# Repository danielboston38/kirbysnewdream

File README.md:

# Link to Video

A replacement for the RF modulator in the original Nintendo Entertainment System (NES-001). Drops into the stock RF module slot inside the shell and provides composite video and USB-C power in place of a part that fails by design.

> **Renamed.** This project shipped its first revision as **Kirby's New Dream**.
> From v2 onward it is **Link to Video**. Anything referring to the old name —
> the v1 board silkscreen, the 2026-07-16 PCBWay fab package under
> [`pcbway_production/`](./pcbway_production), and older commits — is the same
> project. The GitHub repository was renamed to match; the previous
> `kirbysnewdream` URL still redirects.

## Why this board exists

The NES-001's RF modulator already carries composite video, so this isn't about
adding an output the console lacks. It's about replacing a part that reliably
destroys itself.

Nintendo packed the modulator's regulator and RF stages into a sealed can with no
ventilation. It cooks its own electrolytics, they leak, and the electrolyte eats
the traces underneath. Across three NES-001 units on the author's bench, **all
three** had modulator failures from exactly this — including a Mitsumi unit that
looked pristine externally and had every capacitor leaking inside.

So the modulator is a consumable on a forty-year-old console, and the usual
options are to recap a corroded board or to fit an aftermarket board. This is the
second option, with the power input modernised to USB-C while the slot is open.

## Disclosure

This project's schematic design, debugging, and documentation were developed with the assistance of AI (Claude, by Anthropic). All hardware was hand-assembled, tested, and validated by the author. Use, review, and verify independently before building.

## Status

🟡 First prototype assembled and power-tested successfully (5V confirmed clean on rail, no protection trips). Video output path **does not work on v1 hardware** — traced to a schematic defect in which Q1's emitter node was shorted to the +5V rail (see Known Issues). Fixed in source; v1 boards need a rework.

<!-- Swap the line above for something like this once video's confirmed:
🟢 Fully validated — power and composite video both confirmed working on hardware.
-->

## Features

- USB-C power input (power only — no data lines)
- Composite video output
- Active overcurrent protection — TPS2553 eFuse with a ~1.18 A resistor-programmed limit, soft-start and thermal shutdown, backed by a polyfuse
- Fits inside the original NES shell at the stock RF module location
- Bring-up test points for video, ground, +5V and audio, labelled on the silkscreen
- Feed header for an external 8-pin mini-DIN RGB connector (NESRGB)
- All resistor and capacitor values printed on the silkscreen — the v1 board had four identical unlabelled axial footprints carrying four different values, which caused three separate wrong-resistor build errors
- 2-layer PCB, designed in KiCad

## Power path

```
USB-C  ──  F1 polyfuse  ──  U1 TPS2553 eFuse  ──  +5V rail  ──  J4.3 → NES
  VBUS      2.0A hold        ~1.18A limit          C1 100µF
            3.8A trip        soft-start            D1 TVS
            (backup)         thermal shutdown
```

F1 alone trips at 3.8 A, which protects nothing on a console that draws
roughly 0.5–0.7 A. U1 is the real protection; F1 stays as a backup in case
the eFuse ever fails short.

The current limit is set by R6 on U1's ILIM pin. The relationship is
**inverse** — a larger resistor gives a *lower* limit:

| R6 | Limit (typ) |
|---|---|
| 15 kΩ | 1700 mA |
| 20 kΩ | 1295 mA |
| **22 kΩ (fitted)** | **~1180 mA** |
| 49.9 kΩ | 520 mA |
| 210 kΩ | 130 mA |

Roughly I_OS(A) ≈ 25.9 / R6(kΩ), valid over TI's recommended 15 kΩ–232 kΩ.

U1's EN (pin 3) is active-high and tied to its own input, so the switch is
always on. FAULT (pin 4) is an open-drain output left unconnected — there is
nothing inside a closed NES shell to indicate to. If you want fault
indication, it can sink 25 mA directly.

A useful side effect: D1 is a unidirectional TVS, so fitting it backwards
puts a forward-biased diode across the 5 V rail. Before U1 that was a near
short relying on a polyfuse taking seconds to react. Now the eFuse current-
limits it at ~1.18 A and thermally shuts down, so the mistake is
self-limiting rather than destructive.

## Test points (v2)

Four through-hole test points (2.0 mm pad, 1.0 mm drill) for bring-up. They accept
a 0.64 mm square header pin, so you can solder pins in and use scope grabbers.

The silkscreen carries the signal name only — `VIDEO`, `GND`, `+5V`, `AUDIO` — so
the board reads without this table. The refdes lives on F.Fab for the fab drawings.
(On v2's first pass this was backwards: the signal names were on F.Fab, which never
reaches the physical board, so the silkscreen said only `TP1`–`TP4`.)

| TP  | Net          | Location (mm) | Notes |
|-----|--------------|---------------|-------|
| TP1 | `/VIDEO_OUT` | 62.0, 60.0    | Jack-side video, i.e. after C2 and the 75 Ω series R5 — what the TV actually sees. A high-impedance probe reads roughly double the terminated amplitude. |
| TP2 | `GND`        | 58.5, 60.0    | Straight into the B.Cu ground pour. |
| TP3 | `/5V`        | 52.0, 43.1    | Sits directly on the protected 5 V trunk, downstream of F1 and the TPS2553. |
| TP4 | `/AUDIO_OUT` | 65.9, 28.35   | Audio pass-through between J4 pin 2 and J2. |

The whole back layer is a ground pour, so TP2's position is a convenience, not a
constraint — you can clip a ground lead to any B.Cu feature.

To probe the buffer itself rather than its output, use Q1's emitter leg directly;
there is no test point on `Net-(Q1-E)`.

## RGB output (v2)

Provision for the [NESRGB](https://etim.net.au/nesrgb/) board's RGB connector —
the Micomsoft XRGB-mini Framemeister 8-pin mini-DIN standard.

The connector itself is **not** on this board. The NESRGB kit ships it as a
panel-mount jack that epoxies into a 12 mm hole in the shell, so this board just
feeds it. R/G/B run directly from the NESRGB to the connector; we supply the
other three pins on **J5**:

| J5 pin | Net          | mini-DIN pin | |
|--------|--------------|--------------|---|
| 1 | `/RGB_VIDEO` | 3 | Composite video / sync, 75 Ω terminated |
| 2 | `GND`        | 4 | |
| 3 | `/5V`        | 5 | Downstream of the TPS2553, so it is current-limited |

mini-DIN pins 1 and 2 are N/C; pins 6, 7 and 8 are Blue, Green and Red from the
NESRGB. Note the standard carries no audio — that stays on the RCA jack, which is
deliberate on Tim Worthington's part (it keeps video noise out of the audio).

**Why R7 exists.** The video buffer's output (`/VIDEO_BUF`, Q1's emitter through
C2) now feeds two outputs. Each needs its own 75 Ω source termination: R5 for the
RCA jack, R7 for the mini-DIN. Tying both to one resistor would put two 75 Ω loads
in parallel and halve the amplitude whenever both cables are plugged in.

**One output at a time.** Composite and RGB are an either/or — the design does not
target using both at once. Whichever cable is plugged sees a correct 75 Ω source,
and the unused branch is an unloaded stub.

If both are ever plugged in simultaneously, R7 means each still gets a properly
terminated 75 Ω source rather than the halved amplitude you'd get from sharing one
resistor. Q1's drive is the limit in that case, and it is why **R1 is 220 Ω from
v2** rather than the original 330 Ω. Simulated in ngspice with 2 Vpp at the tap
and both outputs terminated: at 330 Ω the follower clips the positive (white)
peaks by 33 %, at 220 Ω by 11 %. With a single output loaded — the supported
mode — 220 Ω is clean and symmetric (+0.439 / −0.447 V at the jack). Simulated,
not measured on hardware, and still not a supported mode.

## Hardware

- Designed in KiCad (schematic + PCB source included in this repo)
- Fabricated via PCBWay
- See [BOM.csv](./BOM.csv) for full parts list

## Build Notes / Known Issues (v1)

- **Q1 emitter node shorted to +5V (breaks video).** Q1's emitter is clamped to the rail, so C2 couples +5V — not video — into R5/J3. The exact wiring differs by revision: in the repo's pre-v1.1 source R1 had *both* ends on `/5V`, while the fabbed 2026-07-16 boards have R1 pad 1 on `/5V` and pad 2 on a separate net with C1 only. Root cause: an R2 (110Ω) was deleted from the schematic on 2026-07-04, and KiCad merged the two leftover collinear wire stubs into one wire, welding the emitter node to `/5V`. Fixed in source as of v1.1. **Rework for an existing board** (applies to the boards fabbed from the 2026-07-16 gerbers, whose IPC netlist reads `/5V = J4.3, F1.1, R1.1, Q1.1, C2.1, D1.1` and `Net-(C1-Pad1) = R1.2, C1.1`):

That revision has two defects — Q1's emitter is clamped to the rail, *and* C1 only reaches the rail through R1, so the bulk cap decouples nothing. Both are fixed together:

**Confirm the diagnosis before you cut.** Power off, unplugged, caps discharged.
Probe +5 V at J4 pin 3 or D1's K-marked lead. Two measurements, mirror images of
each other:

| Measurement | Defective board | Correctly wired |
|---|---|---|
| Q1 emitter → +5 V | **~0 Ω** | ~330 Ω (R1) |
| C1 **+** terminal → +5 V | **~330 Ω** (stranded behind R1) | ~0 Ω |

After the rework these swap. To identify Q1's legs without relying on the TO-92
orientation: the leg reading 0 Ω to GND is the collector, the leg with continuity
to J4 pin 1 is the base, and the remaining one is the emitter.

Two tests that look useful but are not:

- **Emitter → J3 tip.** C2 blocks DC, so this reads open either way.
- **C1 + → Q1 emitter.** Reads ~330 Ω on a good board *and* a bad one, because R1
  sits between them in both wirings. It cannot distinguish the two.

Powered, the fastest single check is DC at Q1's emitter: roughly 1.5–3 V if
correct, sitting at exactly the rail voltage if shorted.

**R1's left pad is a star point.** Three things meet there: F1 (the source), the
D1 + J4.3 branch (the load), and Q1's emitter. The two incoming rail traces are
*collinear*, so a single cut severs both — which is why this needs **two**
jumpers, not one.

1. **Cut** the 0.8 mm trace leaving R1's left pad toward the **upper left**, about
   5–8 mm from the pad. Leave the trace entering from the upper right — that is
   Q1's emitter and must stay. Stay below the level of D1's cathode; above that
   point only one of the two overlapping traces is present, and you need both cut.

2. **Two jumpers.** The cut leaves three islands that must all become one rail:

   | Island | Pads |
   |---|---|
   | A | C1's **+** pad, R1's **right** pad |
   | B | F1 pad 1 (left pad, trace toward D1 — not the USB-C side) |
   | C | D1's cathode (K), J4 pin 3 |

   Any two wires joining all three work. One wire per pad:
   - **C1+ → F1 pad 1** (~14 mm)
   - **R1's right pad → D1 cathode** (~25 mm)

   Do this with R1 removed — its right pad is far easier to solder empty.

3. **Fit R1 = 300–330 Ω.** Check the part before fitting: R1, R3, R4, R5 (and R7
   on v2) all share the same `R_Axial_DIN0207` footprint in four different values,
   and the v1 silkscreen prints no values. At least one board was built with a
   5.1 kΩ from the R3/R4 pile in R1, which gives ~0.6 mA of standing current
   instead of ~9 mA — enough to look plausible and still produce no usable video.

4. **Confirm R5 (75Ω) is populated.** Across R5's own pads should read ~75 Ω; it
   has no parallel path in circuit (C2 blocks DC on one side, the jack is open on
   the other), so it doubles as a meter sanity check.

5. **Fit the transistor last.** Powering the board before the cut is done drives
   Q1 into saturation from the rail straight to ground with no current limit — see
   below.

Verify with a meter before powering: R1's left pad to D1 cathode must now read
**open**; R1's left pad to F1 pad 1 must read **~330Ω** through R1; R1's left pad
must still show continuity to Q1's emitter and C2 pin 1; and D1's cathode must
read **~0 Ω** to J4 pin 3 *and* to F1 pad 1. Powered, Q1's emitter should sit near
1.5–3V — a reading of 5V means the cut did not take.

**The short destroys transistors.** With the emitter clamped to +5 V and the base
at the NES's video level, the B-E junction is forward-biased by 3–4 V, so Q1
saturates with its collector tied directly to ground and nothing limiting the
current. Q1 is a 150 mA part; F1 does not trip until 3.8 A. Every power-up in that
state risks another transistor, which is the likely fate of the first one.
- F1 (polyfuse) footprint field in KiCad is mislabeled as a polarized capacitor footprint despite correct value — cosmetic/documentation issue only, does not affect function. Fix planned for v2.
- Video/audio RCA jack mounting holes are slightly asymmetric — cosmetic only, doesn't affect NES shell fit.
- v1 silkscreen doesn't include component value labels or Q1 pin markers (E/C/B). **Values are on the silkscreen from v2.** On v1 this caused three separate wrong-resistor errors in R1 (a 5.1kΩ and an 820Ω both fitted before the right value went in) because R1/R3/R4/R5/R7 share one footprint across four values. Q1 pin markers are still outstanding.
- **D1 does not protect U1.** The fitted TVS is a Littelfuse 1.5KE6.8A: stand-off 5.80 V, breakdown 6.45–7.14 V at 10 mA, clamping 10.5 V at 144.8 A. The TPS2553's absolute maximum on IN and OUT is 7 V, so the TVS has barely begun conducting by the time the eFuse is already out of spec, and under a real surge it lets the rail reach 10.5 V. D1 protects the console downstream; it will not save U1. Repositioning D1 doesn't help — both U1 pins share the same 7 V rating — and no avalanche TVS clamps below 7 V while standing off USB-C's 5.5 V worst case. Proper protection needs a switch with integrated overvoltage cutoff. Deferred to v3 — v2 ships with this gap.
- D1's symbol (`Diode:1.5KExxA`) names both pins A1/A2 and draws no cathode — KiCad uses identical pin naming for the unidirectional and bidirectional variants of this part. Polarity comes only from the footprint silkscreen band, which is at the pad-1 (+5 V) end and is correct. Watch this when hand-assembling.

## Video input biasing

Q1's base is DC-coupled straight to the NES video line, with no bias network on
this board. That is deliberate, and it took a long bench session to establish
why it works.

**The NES mainboard supplies a 1 kΩ pulldown on its video output pin.** Measured
in circuit at 0.999 kΩ, identical with the meter leads both ways — a real
resistor, not a semiconductor junction. Q1's base sources roughly 46 µA, which
that 1 kΩ absorbs in about 46 mV. The base cannot float up and Q1 cannot cut off.

This is the same reason Nintendo's own modulator has no base pulldown either. It
also matches the load Nintendo presented on that pin: a 330 Ω series resistor
into a 5.6 kΩ / 330 Ω divider, roughly 500 Ω in total. The NES is built to drive
a few hundred ohms.

**So no base pulldown, and no input coupling cap.** If you are adapting this
design to something other than an NES-001, measure that pin to ground first —
if it reads open, you need a pulldown (~47 kΩ) and this board does not have one.

**R2 (330 Ω) is not a bias resistor.** It sits in series between J4 pin 1 and
Q1's base, mirroring the 330 Ω Nintendo places in the same position. Against
Q1's ~21 kΩ base input impedance it costs nothing in signal terms; what it buys
is fault-current limiting into the base-emitter junction, whose reverse rating
is only 5 V.

## Design checks

Two safety nets sit alongside ERC and DRC, both aimed at faults this board has
actually shipped with.

### `tools/check_nets.py`

```
python3 tools/check_nets.py
```

Exports the schematic netlist, reads the PCB's pad nets, confirms the two agree,
and asserts a set of invariants — chief among them that **Q1's emitter is not on
any power net**. That was the v1 fault: the emitter follower's output was tied
to +5V along with J4.3, D1.1 and F1.1, so Q1 saturated into a grounded collector
with nothing limiting the current. It destroyed a transistor on every power-up.

**ERC and DRC both passed cleanly on that board.** Neither can see that a net is
*wrong*, only that it is internally consistent — which is exactly why this check
exists. Run it before generating a fab package. Gerbers carry no net information,
so once you have them the mistake is invisible.

### `nes_power_video.kicad_dru`

Custom DRC rules covering the geometric half: extra clearance between Q1's
emitter and base nodes and the supply rails, and between the two USB-C
configuration channels. These catch the layout-adjacency version of the same
mistakes. They cannot catch a wrong net assignment — DRC has no view of design
intent — which is what the script above is for.

## Assembly

<!-- Add step-by-step or reference photos here once you've got a documented build process -->

Refer to BOM.csv for exact part values and footprints. Every component carries
its sourcing data in two places, kept in step: the `Manufacturer`, `MPN`,
`LCSC`, `Supplier Link` and `Datasheet` fields on the schematic symbol, and
the matching columns in `BOM.csv`. Jellybean passives have no manufacturer
part number by design — they carry a `Spec` field instead (tolerance, rating,
package) and any part meeting it will do. To pull the fields straight out of
the schematic:

```
kicad-cli sch export bom --group-by '' \
    --fields 'Reference,Value,Manufacturer,MPN,LCSC,Datasheet,Supplier Link,Spec' \
    -o bom.csv nes_power_video.kicad_sch
```

Key notes:
- D1 (zener/TVS): cathode (banded end) toward VBUS/+5V side. From v2 the
  silkscreen prints the value actually fitted, `1.5KE6.8A`; before that it
  printed the generic KiCad symbol name `1.5KExxA`, which is not orderable.
- Q1 (**2SA733**, PNP): flat side facing viewer, leads down = Emitter-Collector-Base, left to right.
  This replaces the 2SA1015/KSA1015, **both of which are end of life** (checked 2026-08-29): MCC's
  `2SA1015-GR-AP` is stocked at Mouser but flagged End of Life, and every onsemi `KSA1015` reads
  Obsolete on DigiKey, available only through Rochester Electronics' last-time-buy channel. The
  2SA733 is in current production, shares the E-C-B pin order exactly so it drops straight in, and is
  a better part for a video buffer: f_T 190 MHz typ against the 2SA1015's 80 MHz, C_ob 2–3 pF, P_C
  750 mW, with the same V_CEO −50 V / I_C −150 mA / V_EBO −5 V — so R2 still guards the base-emitter
  junction exactly as before. Buy the UTC `2SA733L-P-T92-B` from LCSC (**C5310429**, ~$0.035); rank P
  is hFE 200–400, which matches the ~46 µA base current measured on the bench, so the bias point does
  not move. DigiKey's Renesas 2SA733 is Rochester stock at $1.90 — same trap, different part.
- **Why not a 2N3906 or BC557?** Not for the reason you might assume. Electrically the 2N3906 is
  perfectly happy here — V_CEO −40 V, I_C −200 mA, f_T 250 MHz, V_EBO −5 V, hFE 100–300 at 10 mA,
  every figure with huge margin against a 5 V rail at ~9.3 mA. The problem is the middle pin. Per
  UTC's ordering tables, the 2N3906 is **E-B-C** and the 2SA733 is **E-C-B**: the 3906 puts *base* in
  the centre where this board wants *collector*. Turning the part around gives C-B-E — base is still
  in the middle, so no orientation fixes it and you would have to cross two leads. On a v3 layout the
  pin order is free and the 2N3906 becomes a fine choice; on this board it is not. Pin order is a
  manufacturer's choice rather than a standard, so check the datasheet of the exact brand you buy.
- R1 (220Ω): emitter load for Q1 — one end to +5V, the other to the Q1 emitter / C2 node. Not both ends to +5V. Lowered from 300Ω in v2 to raise the drive current: at the assumed ~1.3 V base, 300–330Ω supplies only ~6.2 mA at peak white against the ~6.7 mA the 150Ω load wants. Retune if the measured DC at J4 pin 1 differs from ~1.3 V.
- R2 (330Ω): series resistor in the video input line, between J4 pin 1 and Q1's base. See [Video input biasing](#video-input-biasing).
- **Trim all through-hole leads flush.** The board sits in the RF module slot with shielding immediately below it. Long clipped leads on the underside will short against the can — on the prototype this presented as an intermittent supply trip that only appeared when the board was moved.
- C2 (470µF): not 100µF. Into the 150Ω load, 100µF gives τ=15 ms against the 16.7 ms field period and tilts the picture top to bottom. 470µF gives τ=70 ms.
- F1 (polyfuse): sits with slight standoff above PCB by design — this is normal for radial-lead parts, not a defect.
  **No KiCad footprint exists for the Littelfuse RHEF series**, so F1 borrows `Fuse:Fuse_Bourns_MF-RG300`:
  pads 5.24 mm centre-to-centre with 1.01 mm drills. The RHEF200's 0.51 mm leads at 5.05 ±0.75 mm
  spacing fit that comfortably, but the Bourns device is rated 3.0 A/5.1 A and the silkscreen outline is
  *its* body — treat the outline as indicative, not as a clearance boundary. Drawing a true RHEF200
  footprint would move pad 2 by ~1.2 mm and force a re-route, so it is a v3 job, not a patch.
- USB-C1: GCT USB4970-00-A, SMD receptacle — power-only, no data lines. KiCad has no USB4970
  footprint, but GCT's USB4970 drawing specifies the same recommended land pattern as the USB4125
  (pad centres 1.00/3.04/5.50 mm, shell holes 8.64 × 3.80 mm apart), so
  `Connector_USB:USB_C_Receptacle_GCT_USB4125-xx-x` is the right footprint. Use the **plain** variant:
  USB4970-00-A takes the 1.00 mm shell stake, and `-0190` is the 1.90 mm stake part. Pad geometry is
  identical between the two, so this is a naming correction, not a layout change.
- U1 (TPS2553, SOT-23-6): pin 1 is IN, marked by the dot on the package. Pin order is IN, GND, EN down one side and OUT, ILIM, FAULT up the other. Order the plain TPS2553DBVR — the `-1` suffix is the latch-off variant, which would need a power cycle after every trip instead of retrying automatically.
- C3 (100nF, 0805): TI requires this as close to U1 pin 1 as the layout allows. It sits immediately left of U1.
- R6 (22k, 0805): sets the current limit — see the table above before substituting.

## Certification

This project is **OSHWA-certified open source hardware**, UID **[US002842](https://certification.oshwa.org/us002842.html)**.

The certification confirms that the design files, schematics, PCB layout, bill of
materials and documentation in this repository are published under an
OSI/FSF-approved open licence and are complete enough for someone else to study,
modify, manufacture and distribute the hardware. See the
[OSHWA certification directory entry](https://certification.oshwa.org/us002842.html)
for the registered details.

The certification mark above is
[`certification-mark-US002842-stacked.svg`](./certification-mark-US002842-stacked.svg),
issued by OSHWA for this UID. It applies to this design only — it is not
transferable to derivatives, which need their own certification.

## License

Licensed under [CERN-OHL-S v2](./LICENSE.txt) (strongly reciprocal open hardware license). See [LICENSE](./LICENSE.txt).

## Photos

<!-- Add build photos here -->

## Acknowledgments

<!-- Optional: credit anyone who helped with debugging, Discord community, etc. -->

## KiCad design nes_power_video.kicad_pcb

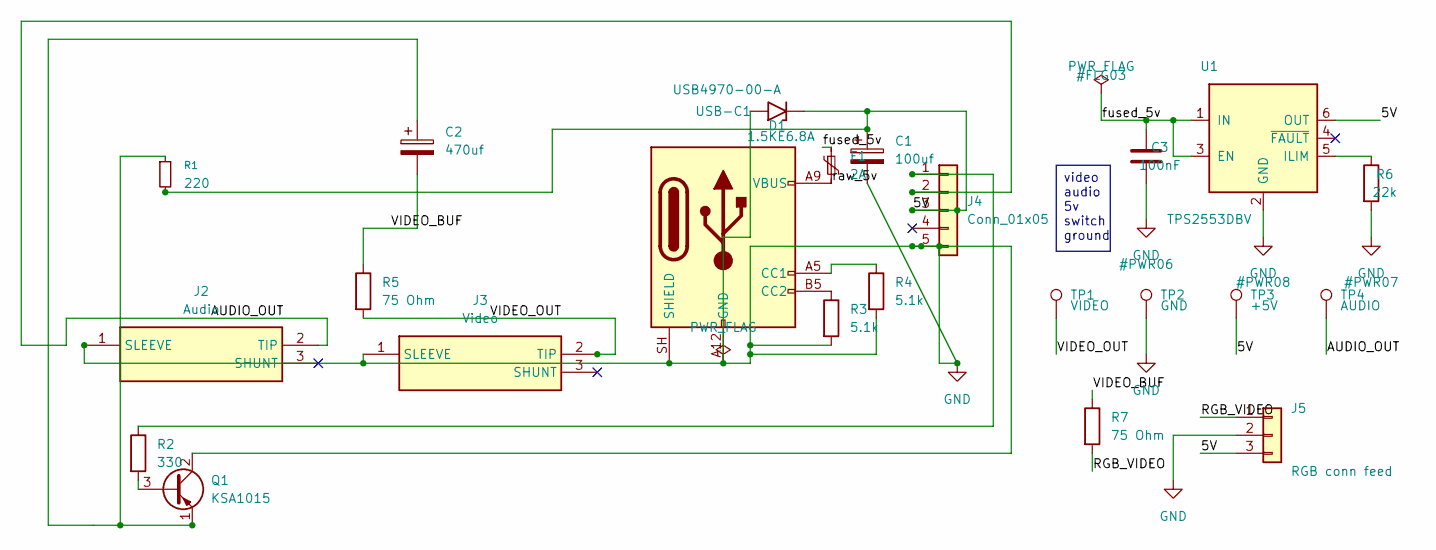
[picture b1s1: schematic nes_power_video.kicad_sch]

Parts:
C1: 100uf; CP_Radial_D10.0mm_P5.00mm
C2: 470uf; CP_Radial_D10.0mm_P5.00mm
C3: 100nF; C_0805_2012Metric_Pad1.18x1.45mm_HandSolder; MPN CC0805KRX7R9BB104; LCSC C49678
D1: 1.5KE6.8A; D_DO-201AE_P15.24mm_Horizontal; MPN 1.5KE6.8A
F1: 2A; Fuse_Bourns_MF-RG300; MPN RHEF200
J2: Audio; PJRAN1X1U03X; Mouser Part Number 502-PJRAN1X1U03X
J3: Video; PJRAN1X1U03X; Mouser Part Number 502-PJRAN1X1U03X
J4: Conn_01x05; PinHeader_1x05_P2.54mm_Vertical
J5: RGB conn feed; PinHeader_1x03_P2.54mm_Vertical
Q1: KSA1015; TO-92_Inline; MPN KSA1015GRTA
R1: 220; R_Axial_DIN0207_L6.3mm_D2.5mm_P7.62mm_Horizontal
R2: 330; R_Axial_DIN0207_L6.3mm_D2.5mm_P7.62mm_Horizontal
R3, R4: 5.1k; R_Axial_DIN0207_L6.3mm_D2.5mm_P7.62mm_Horizontal
R5, R7: 75 Ohm; R_Axial_DIN0207_L6.3mm_D2.5mm_P7.62mm_Horizontal
R6: 22k; R_0805_2012Metric_Pad1.20x1.40mm_HandSolder; MPN 0805W8F2202T5E; LCSC C17560
TP1: VIDEO; TestPoint_THTPad_D2.0mm_Drill1.0mm
TP2: GND; TestPoint_THTPad_D2.0mm_Drill1.0mm
TP3: +5V; TestPoint_THTPad_D2.0mm_Drill1.0mm
TP4: AUDIO; TestPoint_THTPad_D2.0mm_Drill1.0mm
U1: TPS2553DBV; SOT-23-6_Handsoldering; MPN TPS2553DBVR; LCSC C55266
USB-C1: USB4970-00-A; USB_C_Receptacle_GCT_USB4125-xx-x_6P_TopMnt_Horizontal; MPN USB4970-00-A

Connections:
/5V: C1.1, D1.1 (A1), J4.3, J5.3, R1.2, TP3.1, U1.6 (OUT)
/AUDIO_OUT: J2.2 (TIP), J4.2, TP4.1
/RGB_VIDEO: J5.1, R7.2
/VIDEO_BUF: C2.2, R5.1, R7.1
/VIDEO_OUT: J3.2 (TIP), R5.2, TP1.1
/fused_5v: C3.1, F1.1, U1.1 (IN), U1.3 (EN)
/raw_5v: F1.2, USB-C1.A9 (VBUS), USB-C1.B9 (VBUS)
GND: C1.2, C3.2, D1.2 (A2), J2.1 (SLEEVE), J3.1 (SLEEVE), J4.5, J5.2, Q1.2 (C), R3.2, R4.2, R6.2, TP2.1, U1.2 (GND), USB-C1.A12 (GND), USB-C1.B12 (GND), USB-C1.SH (SHIELD)
unnamed: J4.1, R2.1
unnamed: Q1.3 (B), R2.2
unnamed: C2.1, Q1.1 (E), R1.1
unnamed: R6.1, U1.5 (ILIM)
unnamed: R4.1, USB-C1.A5 (CC1)
unnamed: R3.1, USB-C1.B5 (CC2)

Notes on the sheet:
video audio 5v switch ground

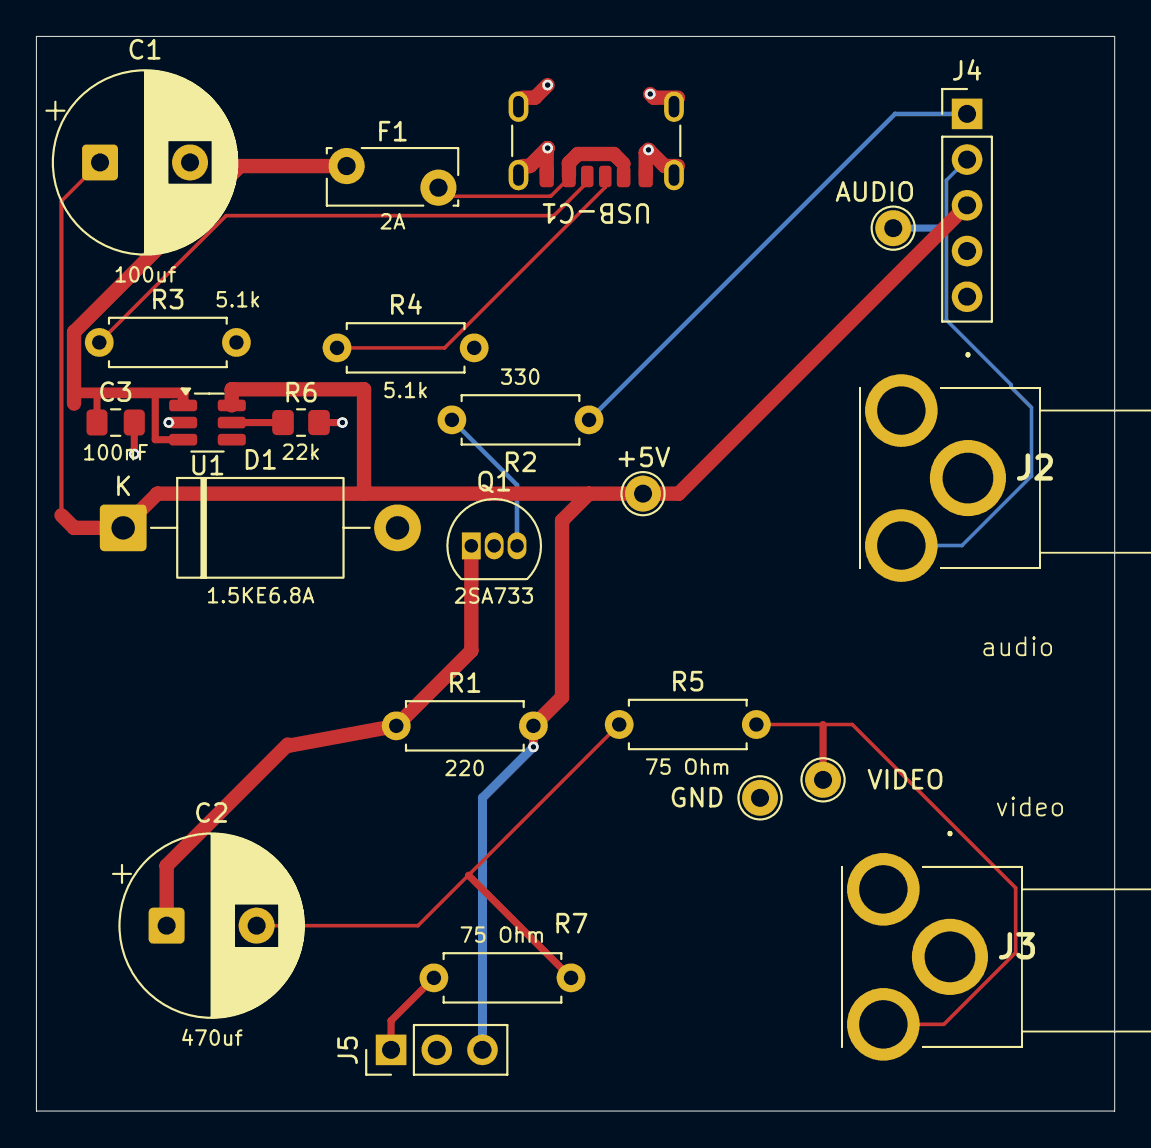
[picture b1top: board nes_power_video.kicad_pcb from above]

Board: 2 copper layers, 59.9 x 59.7 mm, 23 parts (0 on the bottom side), 14 nets.
